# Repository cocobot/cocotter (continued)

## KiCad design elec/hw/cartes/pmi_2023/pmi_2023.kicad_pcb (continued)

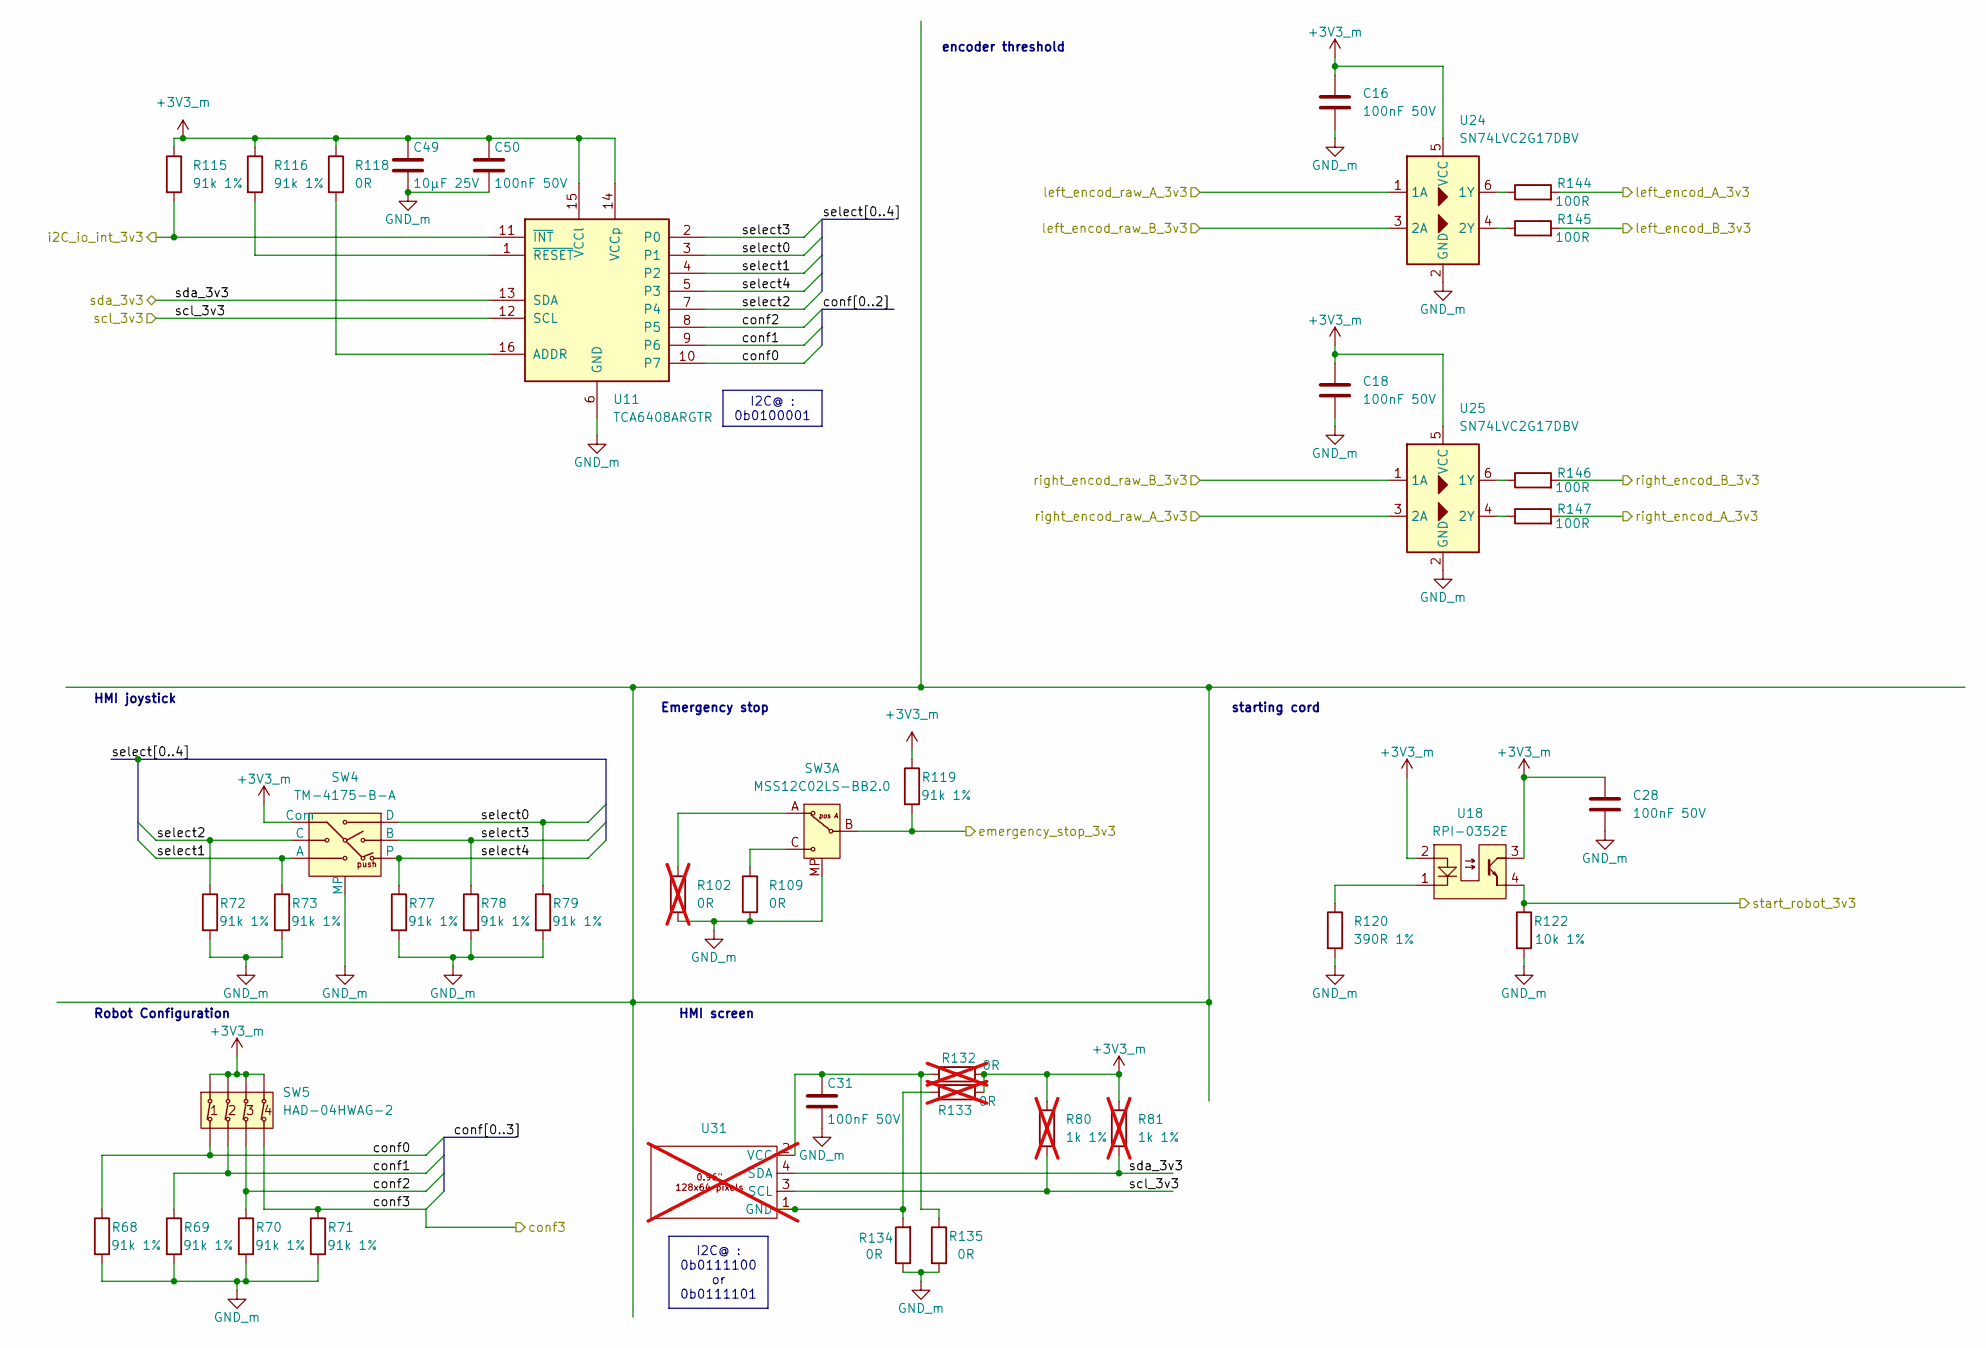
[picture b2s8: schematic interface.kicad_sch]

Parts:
C16, C18, C28, C31, C50: 100nF 50V; C_0603_1608Metric; JLCPCB Part # C14663
C49: 10µF 25V; C_0805_2012Metric; JLCPCB Part # C15850
R68, R69, R70, R71, R72, R73, R77, R78, R79, R115, R116, R119: 91k 1%; r0603_reflow; JLCPCB Part # C23265
R80, R81: 1k 1%; r0603_reflow; mouser 603-RC0603FR-10100KL; not fitted
R102, R132, R133: 0R; r0603_reflow; JLCPCB Part # C431718; not fitted
R109, R118, R134, R135: 0R; r0603_reflow; JLCPCB Part # C431718
R120: 390R 1%; r0603_reflow; mouser 603-RC0603FR-10100KL
R122: 10k 1%; r0603_reflow; mouser 603-RC0603FR-10100KL
R144, R145, R146, R147: 100R; r0603_reflow; JLCPCB Part # C22775
SW3: MSS12C02LS-BB2.0; JLCPCB Part # C3008585
SW4: TM-4175-B-A; DIGIKEY_REF 450-2425755-1TR-ND
SW5: HAD-04HWAG-2; JLCPCB Part # C437204
U11: TCA6408ARGTR; VQFN-16-1EP_3x3mm_P0.5mm_EP1.1x1.1mm; mouser 595-TCA6408ARGTR
U18: RPI-0352E; JLCPCB Part # C509307
U24, U25: SN74LVC2G17DBV; SOT-23-6
U31: OLED_0.96inch; not fitted

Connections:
+3V3_m: C16.1, C18.1, C28.1, C49.1, C50.1, R80.1, R81.1, R115.1, R116.1, R118.1, R119.1, R132.2, R133.2, SW4.5 (Com), SW5.5, SW5.6, SW5.7, SW5.8, U11.14 (VCCp), U11.15 (VCCl), U18.2 (A), U18.3 (C), U24.5 (VCC), U25.5 (VCC); also elsewhere on the board
/boards interface/com/emergency_stop_3v3: R119.2, SW3.B; also elsewhere on the board
/boards interface/com/left_encod_A_3v3: R144.2; also elsewhere on the board
/boards interface/com/left_encod_B_3v3: R145.2; also elsewhere on the board
/boards interface/com/right_encod_A_3v3: R147.2; also elsewhere on the board
/boards interface/com/right_encod_B_3v3: R146.2; also elsewhere on the board
/boards interface/com/start_robot_3v3: R122.1, U18.4 (E); also elsewhere on the board
/boards interface/i2c_io_int_3v3: R115.2, U11.11 (~INT); also elsewhere on the board
/boards interface/interface/conf0: R68.1, SW5.1, U11.10 (P7)
/boards interface/interface/conf1: R69.1, SW5.2, U11.9 (P6)
/boards interface/interface/conf2: R70.1, SW5.3, U11.8 (P5)
/boards interface/interface/conf3: R71.1, SW5.4; also elsewhere on the board
/boards interface/interface/select0: R79.1, SW4.6 (D), U11.3 (P1)
/boards interface/interface/select1: R73.1, SW4.1 (A), U11.4 (P2)
/boards interface/interface/select2: R72.1, SW4.3 (C), U11.7 (P4)
/boards interface/interface/select3: R78.1, SW4.4 (B), U11.2 (P0)
/boards interface/interface/select4: R77.1, SW4.2, U11.5 (P3)
/boards interface/left_encod_raw_A_3v3: U24.1 (1A); also elsewhere on the board
/boards interface/left_encod_raw_B_3v3: U24.3 (2A); also elsewhere on the board
/boards interface/right_encod_raw_A_3v3: U25.3 (2A); also elsewhere on the board
/boards interface/right_encod_raw_B_3v3: U25.1 (1A); also elsewhere on the board
/boards interface/scl_top_3v3: R80.2, U11.12 (SCL), U31.3 (SCL); also elsewhere on the board
/boards interface/sda_top_3v3: R81.2, U11.13 (SDA), U31.4 (SDA); also elsewhere on the board
GND_m: C16.2, C18.2, C28.2, C31.2, C49.2, C50.2, R68.2, R69.2, R70.2, R71.2, R72.2, R73.2, R77.2, R78.2, R79.2, R102.2, R109.2, R120.2, R122.2, R134.1, R135.2, SW3.MP, SW4.MP, U11.6 (GND), U24.2 (GND), U25.2 (GND); also elsewhere on the board
unnamed: R102.1, SW3.A
unnamed: R109.1, SW3.C
unnamed: R120.1, U18.1 (C)
unnamed: R118.2, U11.16 (ADDR)
unnamed: R116.2, U11.1 (~RESET)
unnamed: R144.1, U24.6 (1Y)
unnamed: R145.1, U24.4 (2Y)
unnamed: R146.1, U25.6 (1Y)
unnamed: R147.1, U25.4 (2Y)
unnamed: R133.1, R134.2, U31.1 (GND)
unnamed: C31.1, R132.1, R135.1, U31.2 (VCC)

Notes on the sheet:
I2C@ : 0b0111100 or 0b0111101
I2C@ : 0b0100001
Emergency stop
HMI screen
Robot Configuration
HMI joystick
encoder threshold
starting cord

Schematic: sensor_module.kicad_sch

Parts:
C12, C20, C53, C57, C58, C59: 100nF 50V; C_0603_1608Metric; JLCPCB Part # C14663
C51, C52: 10µF 25V; C_0805_2012Metric; JLCPCB Part # C15850
R38, R39, R44, R45, R101, R125, R126, R127, R129, R130, R131: 91k 1%; r0603_reflow; JLCPCB Part # C23265
R123, R124, R128: 10k 1%; r0603_reflow; mouser 603-RC0603FR-10100KL
R141: 0R; r0603_reflow; JLCPCB Part # C431718
TP14, TP15, TP16, TP17: TestPoint; testpoint-THT-0.5mm
U12: LSM6DSO32XTR; LGA-14_3x2.5mm_P0.5mm_LayoutBorder3x4y; JLCPCB Part # C2655100
U22, U30: VL53L5CXV0GC; VL53L5CX; JLCPCB Part # C3178303

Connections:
+3V3_m: C12.1, C51.1, C52.1, C53.1, C57.1, C58.1, C59.1, R38.1, R39.1, R44.1, R45.1, R101.1, R123.1, R125.1, R126.1, R129.1, R130.1, R141.1, U12.5 (Vdd_IO), U22.A4 (IOVDD), U22.B1 (AVDD), U22.B7 (AVDD), U30.A4 (IOVDD), U30.B1 (AVDD), U30.B7 (AVDD); also elsewhere on the board
/boards interface/Sensor module/VL53L5_I2C_RST_u22_3v3: R124.1, U22.A1 (I2C_RST)
/boards interface/Sensor module/VL53L5_I2C_RST_u30_3v3: R128.1, U30.A1 (I2C_RST)
/boards interface/Sensor module/enable_back_tof_3v3: R131.1, U30.A5 (LPn); also elsewhere on the board
/boards interface/Sensor module/enable_front_tof_3v3: R127.1, U22.A5 (LPn); also elsewhere on the board
/boards interface/Sensor module/gyro_irq_3v3: R38.2, U12.4 (INT1); also elsewhere on the board
/boards interface/Sensor module/gyro_miso_3v3: TP14.1, U12.1 (SDO); also elsewhere on the board
/boards interface/Sensor module/gyro_mosi_3v3: TP15.1, U12.14 (SDA/SDI); also elsewhere on the board
/boards interface/Sensor module/gyro_ncs_3v3: R44.2, TP17.1, U12.12 (/CS_/I3C_EN); also elsewhere on the board
/boards interface/Sensor module/gyro_sck_3v3: TP16.1, U12.13 (SCL/SCK); also elsewhere on the board
/boards interface/scl_top_3v3: U22.C4 (SCL), U30.C4 (SCL); also elsewhere on the board
/boards interface/sda_top_3v3: U22.C3 (SDA), U30.C3 (SDA); also elsewhere on the board
/boards interface/tof_irq_3v3: R123.2, U22.A3 (INT), U30.A3 (INT); also elsewhere on the board
GND_m: C12.2, C20.2, C51.2, C52.2, C53.2, C57.2, C58.2, C59.2, R124.2, R127.2, R128.2, R131.2, U12.6 (GND), U12.7 (GND), U22.A2 (RSVD4), U22.A6 (RSVD1), U22.A7 (RSVD2), U22.B4 (THERM_PAD), U22.C1 (GND), U22.C6 (RSVD3), U22.C7 (GND), U30.A2 (RSVD4), U30.A6 (RSVD1), U30.A7 (RSVD2), U30.B4 (THERM_PAD), U30.C1 (GND), U30.C6 (RSVD3), U30.C7 (GND); also elsewhere on the board
unnamed: R39.2, U12.9 (INT2/DEN)
unnamed: R45.2, U12.3 (SCx)
unnamed: R101.2, U12.2 (SDx)
unnamed: C20.1, R141.2, U12.8 (Vdd)
unnamed: R125.2, R126.2, U22.C2 (RSVD6)
unnamed: R129.2, R130.2, U30.C2 (RSVD6)

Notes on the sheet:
default I2C@ : 0b0101001

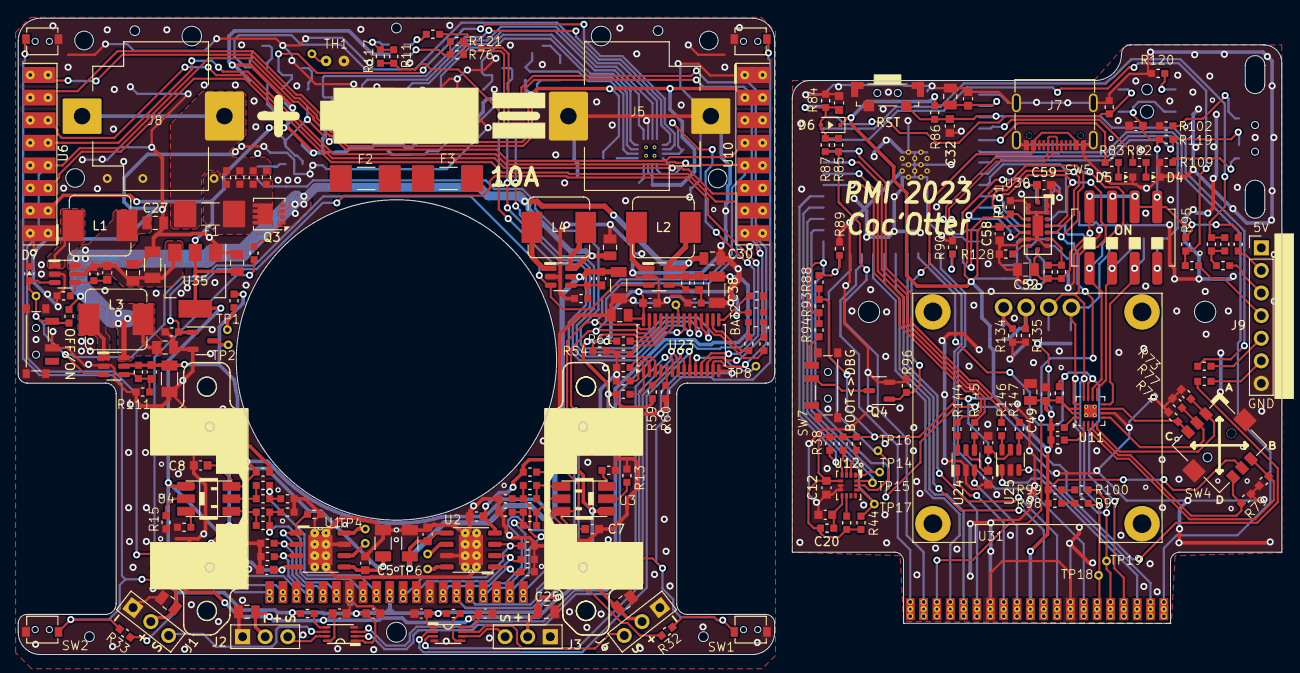
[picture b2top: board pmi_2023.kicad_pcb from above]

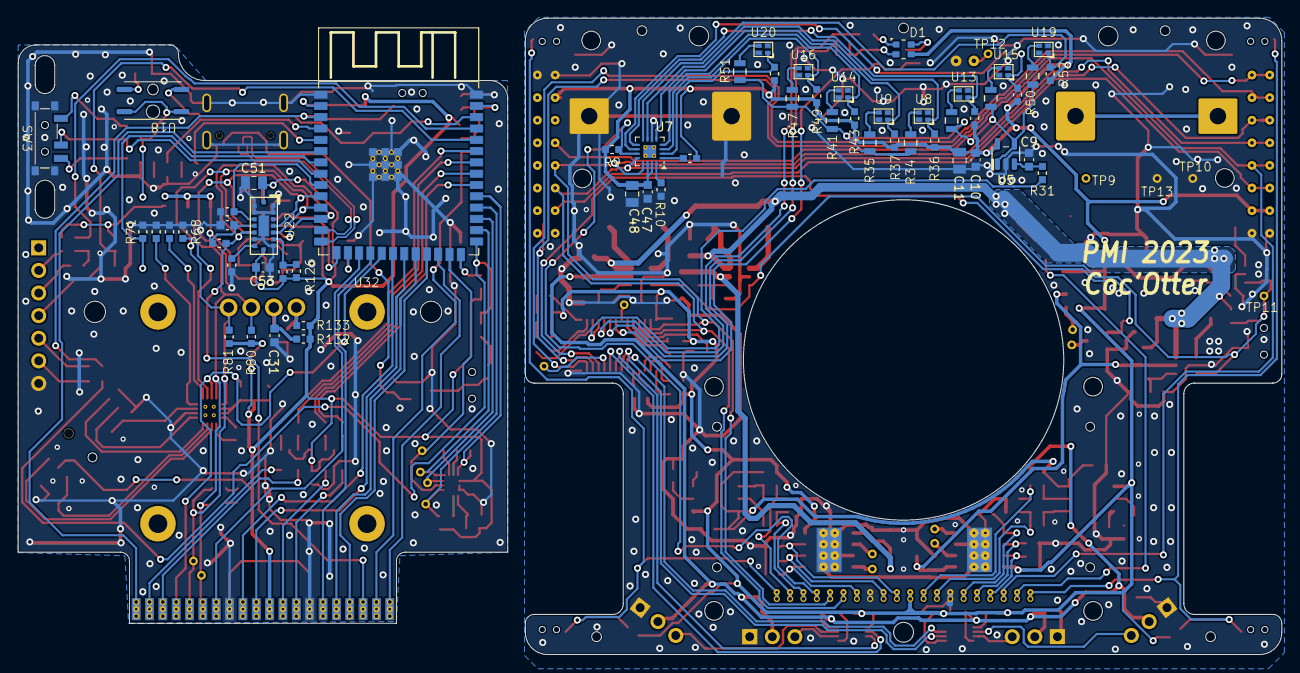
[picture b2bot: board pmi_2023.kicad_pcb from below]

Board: 2 copper layers, 142.0 x 71.5 mm, 294 parts (62 on the bottom side), 192 nets.

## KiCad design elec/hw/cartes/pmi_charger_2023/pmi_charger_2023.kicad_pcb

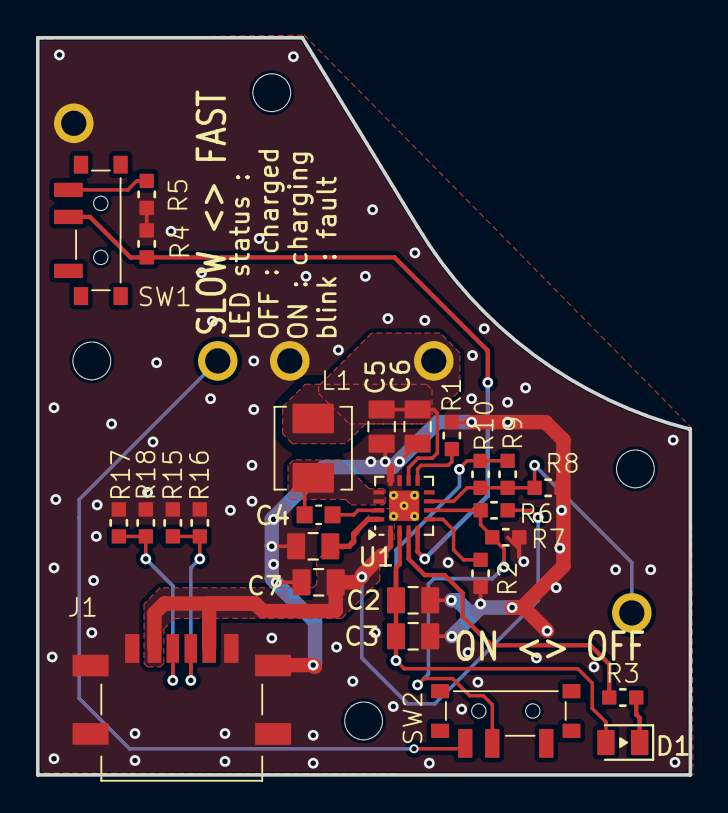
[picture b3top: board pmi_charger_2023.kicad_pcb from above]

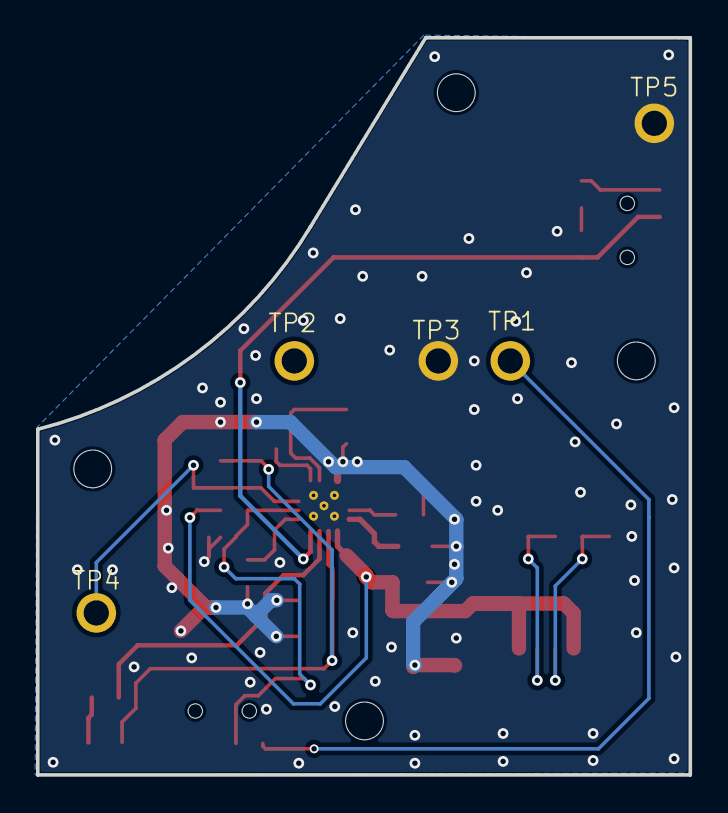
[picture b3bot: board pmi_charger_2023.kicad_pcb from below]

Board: 2 copper layers, 36.2 x 41.0 mm, 36 parts (5 on the bottom side), 18 nets.

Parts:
C1, C5, C6, C7: 10µF 25V; C_0805_2012Metric
C2, C3: 1µF 50V; C_0805_2012Metric
C4: 47nF 50V; C_0603_1608Metric
D1: yellow, 0805; LED_0805_2012Metric
H1, H2, H3, H4: MountingHole_Pad; MountingHole_2.1mm
J1: BTC-TC6S-23
L1: 1µH; SPM4020T
R1: 100k; r0603_reflow
R2: 1k 1%; r0603_reflow
R3: 330R; r0603_reflow
R4: 68k 1%; r0603_reflow
R5, R8: 22k 1%; r0603_reflow
R6, R7, R9, R10, R15, R16, R17, R18: 10k 1%; r0603_reflow
SW1, SW2: MSS12C02LS-BB2.0
TP1, TP2, TP3, TP4, TP5: CPG-07-TH-B
U1: BQ25308RTER; RTE0016C

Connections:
/BAT_TEMP: R8.1, R9.2, R10.2, TP4.1, U1.7 (TS)
/ICHG: R4.1, SW1.B, U1.4 (ICHG)
/POL: R2.1, U1.5 (POL)
/REGN: C2.1, C3.1, D1.A, R9.1, R10.1, U1.2 (REGN)
/bat+: C5.1, C6.1, L1.2, TP2.1, U1.10 (BAT)
/sw: C4.1, L1.1, U1.13 (SW), U1.14 (SW)
//enable_charger: R6.2, R7.2, SW2.B, U1.6 (/EN)
GND: C1.2, C2.2, C3.2, C5.2, C6.2, C7.2, J1.A12 (GND), J1.B12 (GND), J1.SHIELD (SHELL), R1.2, R2.2, R4.2, R5.2, R7.1, R8.2, R15.2, R16.2, R17.2, R18.2, TP3.1, TP5.1, U1.11 (GND), U1.12 (GND), U1.17 (PAD)
unnamed: D1.C, R3.2
unnamed: J1.A5 (CC1), R17.1, R18.1
unnamed: J1.B5 (CC2), R15.1, R16.1
unnamed: R5.1, SW1.C
unnamed: SW2.C, TP1.1
unnamed: C4.2, U1.15 (BTST)
unnamed: C1.1, U1.16 (PMID)
unnamed: R3.1, U1.3 (STAT)
unnamed: R1.1, U1.9 (VSET)
VBUS: C7.1, J1.A9 (VBUS), J1.B9 (VBUS), R6.1, U1.1 (VBUS)
